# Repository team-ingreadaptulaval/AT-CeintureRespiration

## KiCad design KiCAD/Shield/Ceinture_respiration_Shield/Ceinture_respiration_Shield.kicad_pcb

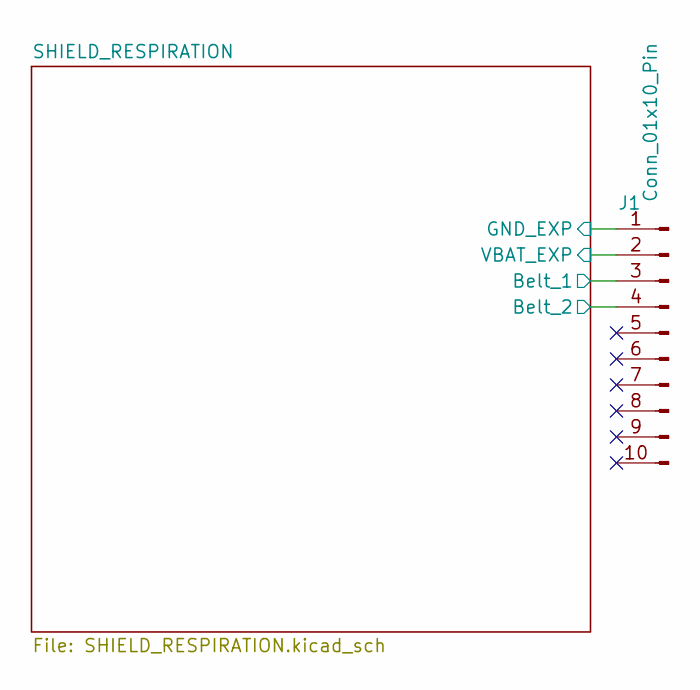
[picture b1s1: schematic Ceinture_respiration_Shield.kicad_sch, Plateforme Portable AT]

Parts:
J1: Conn_01x10_Pin; PinHeader_1x10_P2.54mm_Vertical; LCSC C492409

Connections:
/SHIELD_RESPIRATION/Belt_1: J1.3; also elsewhere on the board
/SHIELD_RESPIRATION/Belt_2: J1.4; also elsewhere on the board
/SHIELD_RESPIRATION/VBAT_EXP: J1.2; also elsewhere on the board
GND_EXP: J1.1; also elsewhere on the board

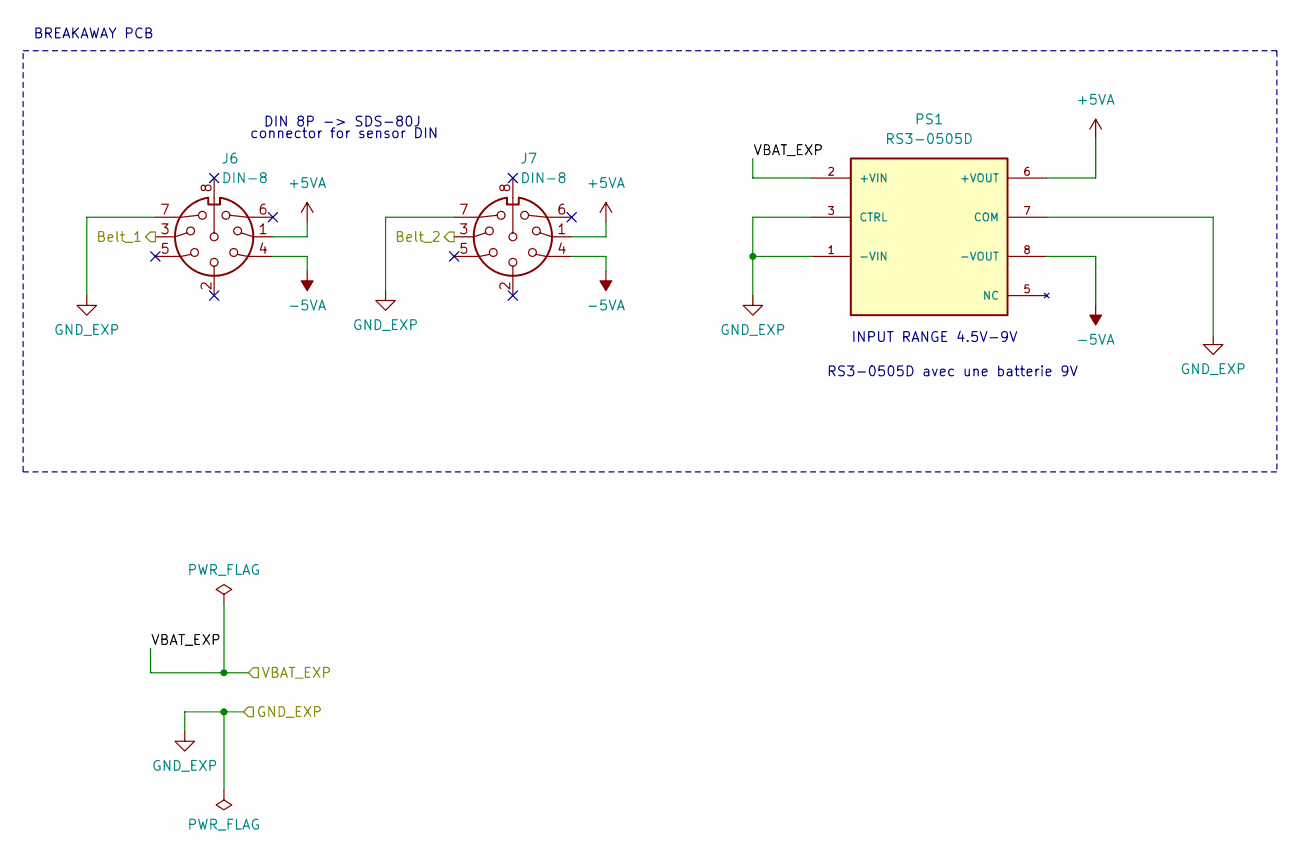
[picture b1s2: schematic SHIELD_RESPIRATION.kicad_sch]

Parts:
J6, J7: DIN-8; CUI_SDS-80J; MPN SDS-80J; Digikey CP-2380-ND
PS1: RS3-0505D; CONV_RS3-0505D; PARTREV 3; Digikey 945-1318-ND

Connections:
+5VA: J6.1, J7.1, PS1.6 (+VOUT)
-5VA: J6.4, J7.4, PS1.8 (-VOUT)
/SHIELD_RESPIRATION/Belt_1: J6.3; also elsewhere on the board
/SHIELD_RESPIRATION/Belt_2: J7.3; also elsewhere on the board
/SHIELD_RESPIRATION/VBAT_EXP: PS1.2 (+VIN); also elsewhere on the board
GND_EXP: J6.7, J7.7, PS1.1 (-VIN), PS1.3 (CTRL), PS1.7 (COM); also elsewhere on the board

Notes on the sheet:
connector for sensor DIN
DIN 8P -> SDS-80J
INPUT RANGE 4.5V-9V
RS3-0505D avec une batterie 9V
BREAKAWAY PCB

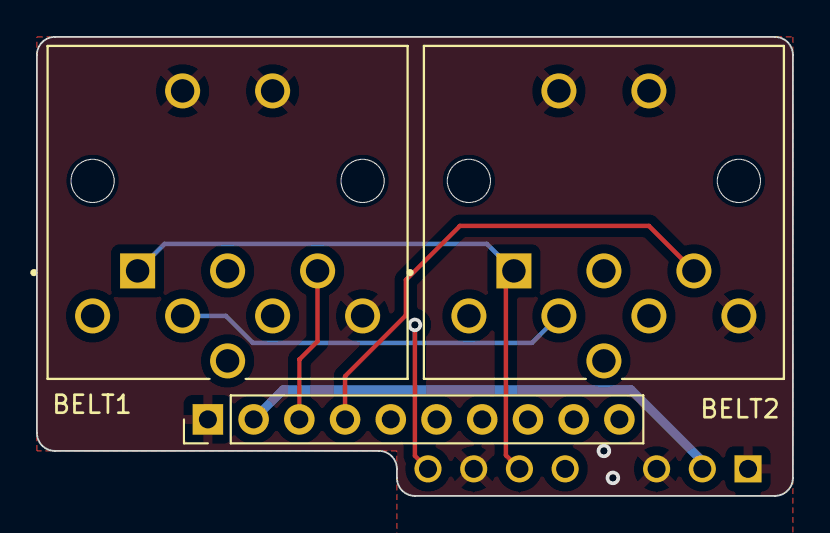
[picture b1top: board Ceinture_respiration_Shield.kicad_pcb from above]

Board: 4 copper layers, 42.0 x 25.5 mm, 4 parts (1 on the bottom side), 6 nets.

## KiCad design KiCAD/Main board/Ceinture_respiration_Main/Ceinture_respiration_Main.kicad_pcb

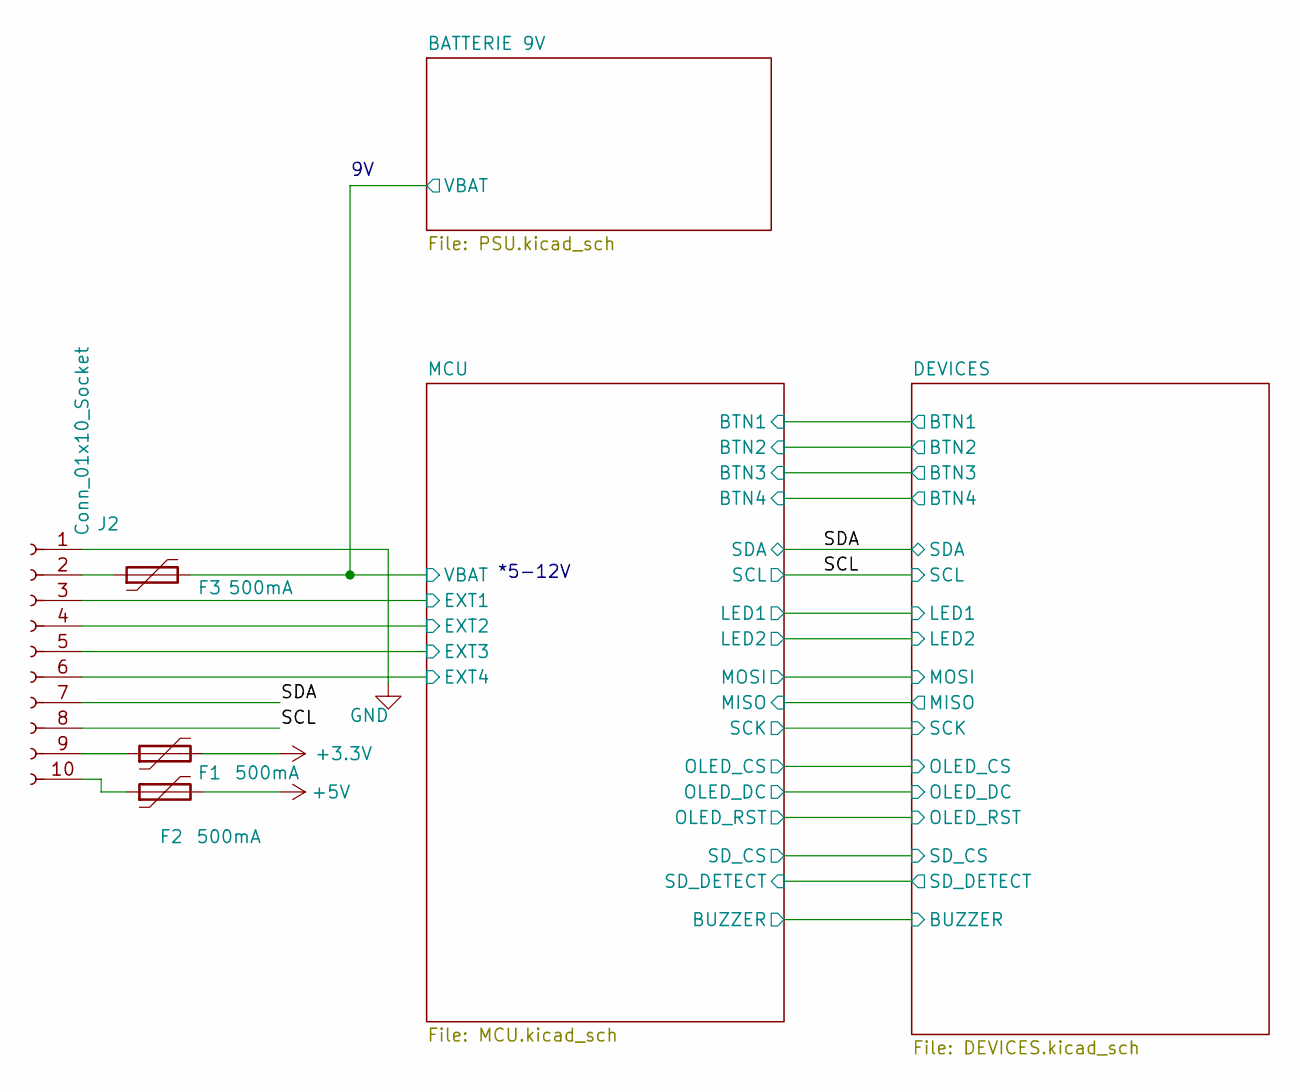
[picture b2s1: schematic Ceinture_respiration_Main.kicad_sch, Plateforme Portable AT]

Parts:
F1, F2, F3: 500mA; Fuse_0603_1608Metric; LCSC C2844464
J2: Conn_01x10_Socket; PinSocket_1x10_P2.54mm_Vertical; LCSC C2897373

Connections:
+3.3V: F1.2; also elsewhere on the board
+5V: F2.2; also elsewhere on the board
/BATTERIE 9V/VBAT: F3.2; also elsewhere on the board
/MCU/EXT1: J2.3; also elsewhere on the board
/MCU/EXT2: J2.4; also elsewhere on the board
/MCU/EXT3: J2.5; also elsewhere on the board
/MCU/EXT4: J2.6; also elsewhere on the board
/SCL: J2.8; also elsewhere on the board
/SDA: J2.7; also elsewhere on the board
GND: J2.1; also elsewhere on the board
unnamed: F3.1, J2.2
unnamed: F1.1, J2.9
unnamed: F2.1, J2.10

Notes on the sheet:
*5-12V

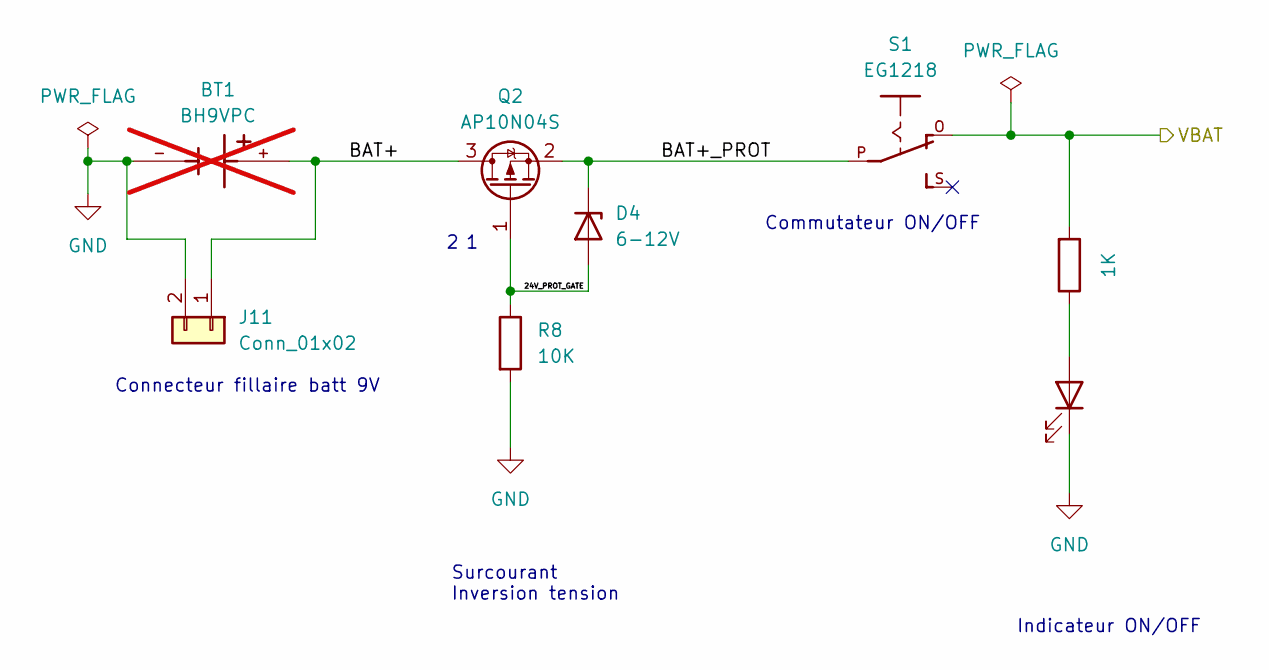
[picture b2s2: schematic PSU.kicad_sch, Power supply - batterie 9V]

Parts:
BT1: BH9VPC; BAT_BH9VPC; PARTREV F; not fitted
D4: 6-12V; D_SOD-323; LCSC C2103
D5: LED; LED_D3.0mm; LCSC C2895472
J11: Conn_01x02; PinHeader_1x02_P2.54mm_Vertical
Q2: AP10N04S; SOT-23; LCSC C15127
R8: 10K; R_0603_1608Metric; LCSC C25804
R9: 1K; R_0603_1608Metric; LCSC C21190
S1: EG1218; MPN EG1218; DigiKey EG1218

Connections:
/BATTERIE 9V/24V_PROT_GATE: D4.2 (A), Q2.1 (G), R8.1
/BATTERIE 9V/BAT+: J11.1, Q2.3 (D)
/BATTERIE 9V/BAT+_PROT: D4.1 (K), Q2.2 (S), S1.P
/BATTERIE 9V/VBAT: R9.2, S1.O; also elsewhere on the board
GND: D5.1 (K), J11.2, R8.2; also elsewhere on the board
unnamed: D5.2 (A), R9.1

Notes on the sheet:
Connecteur fillaire batt 9V
Commutateur ON/OFF
Indicateur ON/OFF
Surcourant Inversion tension

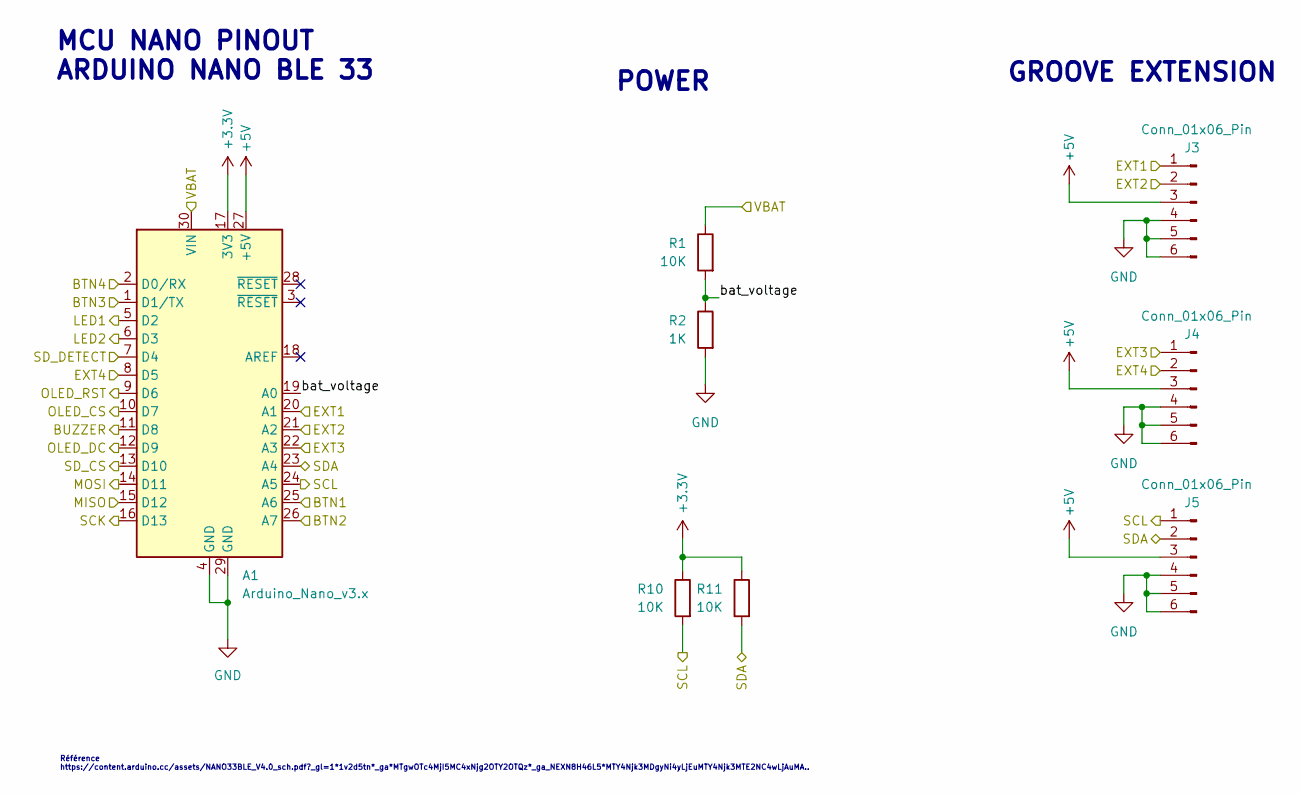
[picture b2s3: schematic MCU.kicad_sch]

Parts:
A1: Arduino_Nano_v3.x; MODULE_ABX00027
J3, J4, J5: Conn_01x06_Pin; CONN4_20164_SEE; MPN Grove Conn
R1, R10, R11: 10K; R_0603_1608Metric; LCSC C25804
R2: 1K; R_0603_1608Metric; LCSC C21190

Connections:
+3.3V: A1.17 (3V3), R10.1, R11.1; also elsewhere on the board
+5V: A1.27 (+5V), J3.3, J4.3, J5.3; also elsewhere on the board
/BATTERIE 9V/VBAT: A1.30 (VIN), R1.1; also elsewhere on the board
/DEVICES/BTN1: A1.25 (A6); also elsewhere on the board
/DEVICES/BTN2: A1.26 (A7); also elsewhere on the board
/DEVICES/BTN3: A1.1 (D1/TX); also elsewhere on the board
/DEVICES/BTN4: A1.2 (D0/RX); also elsewhere on the board
/DEVICES/BUZZER: A1.11 (D8); also elsewhere on the board
/DEVICES/LED1: A1.5 (D2); also elsewhere on the board
/DEVICES/LED2: A1.6 (D3); also elsewhere on the board
/DEVICES/MISO: A1.15 (D12); also elsewhere on the board
/DEVICES/MOSI: A1.14 (D11); also elsewhere on the board
/DEVICES/OLED_CS: A1.10 (D7); also elsewhere on the board
/DEVICES/OLED_DC: A1.12 (D9); also elsewhere on the board
/DEVICES/OLED_RST: A1.9 (D6); also elsewhere on the board
/DEVICES/SCK: A1.16 (D13); also elsewhere on the board
/DEVICES/SD_CS: A1.13 (D10); also elsewhere on the board
/DEVICES/SD_DETECT: A1.7 (D4); also elsewhere on the board
/MCU/EXT1: A1.20 (A1), J3.1; also elsewhere on the board
/MCU/EXT2: A1.21 (A2), J3.2; also elsewhere on the board
/MCU/EXT3: A1.22 (A3), J4.1; also elsewhere on the board
/MCU/EXT4: A1.8 (D5), J4.2; also elsewhere on the board
/MCU/bat_voltage: A1.19 (A0), R1.2, R2.1
/SCL: A1.24 (A5), J5.1, R10.2; also elsewhere on the board
/SDA: A1.23 (A4), J5.2, R11.2; also elsewhere on the board
GND: A1.4 (GND), A1.29 (GND), J3.4, J3.5, J3.6, J4.4, J4.5, J4.6, J5.4, J5.5, J5.6, R2.2; also elsewhere on the board

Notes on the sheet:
MCU NANO PINOUT ARDUINO NANO BLE 33
Référence https://content.arduino.cc/assets/NANO33BLE_V4.0_sch.pdf?_gl=1*1v2d5tn*_ga*MTgwOTc4MjI5MC4xNjg2OTY2OTQz*_ga_NEXN8H46L5*MTY4Njk3MDgyNi4yLjEuMTY4Njk3MTE2NC4wLjAuMA..
GROOVE EXTENSION
POWER

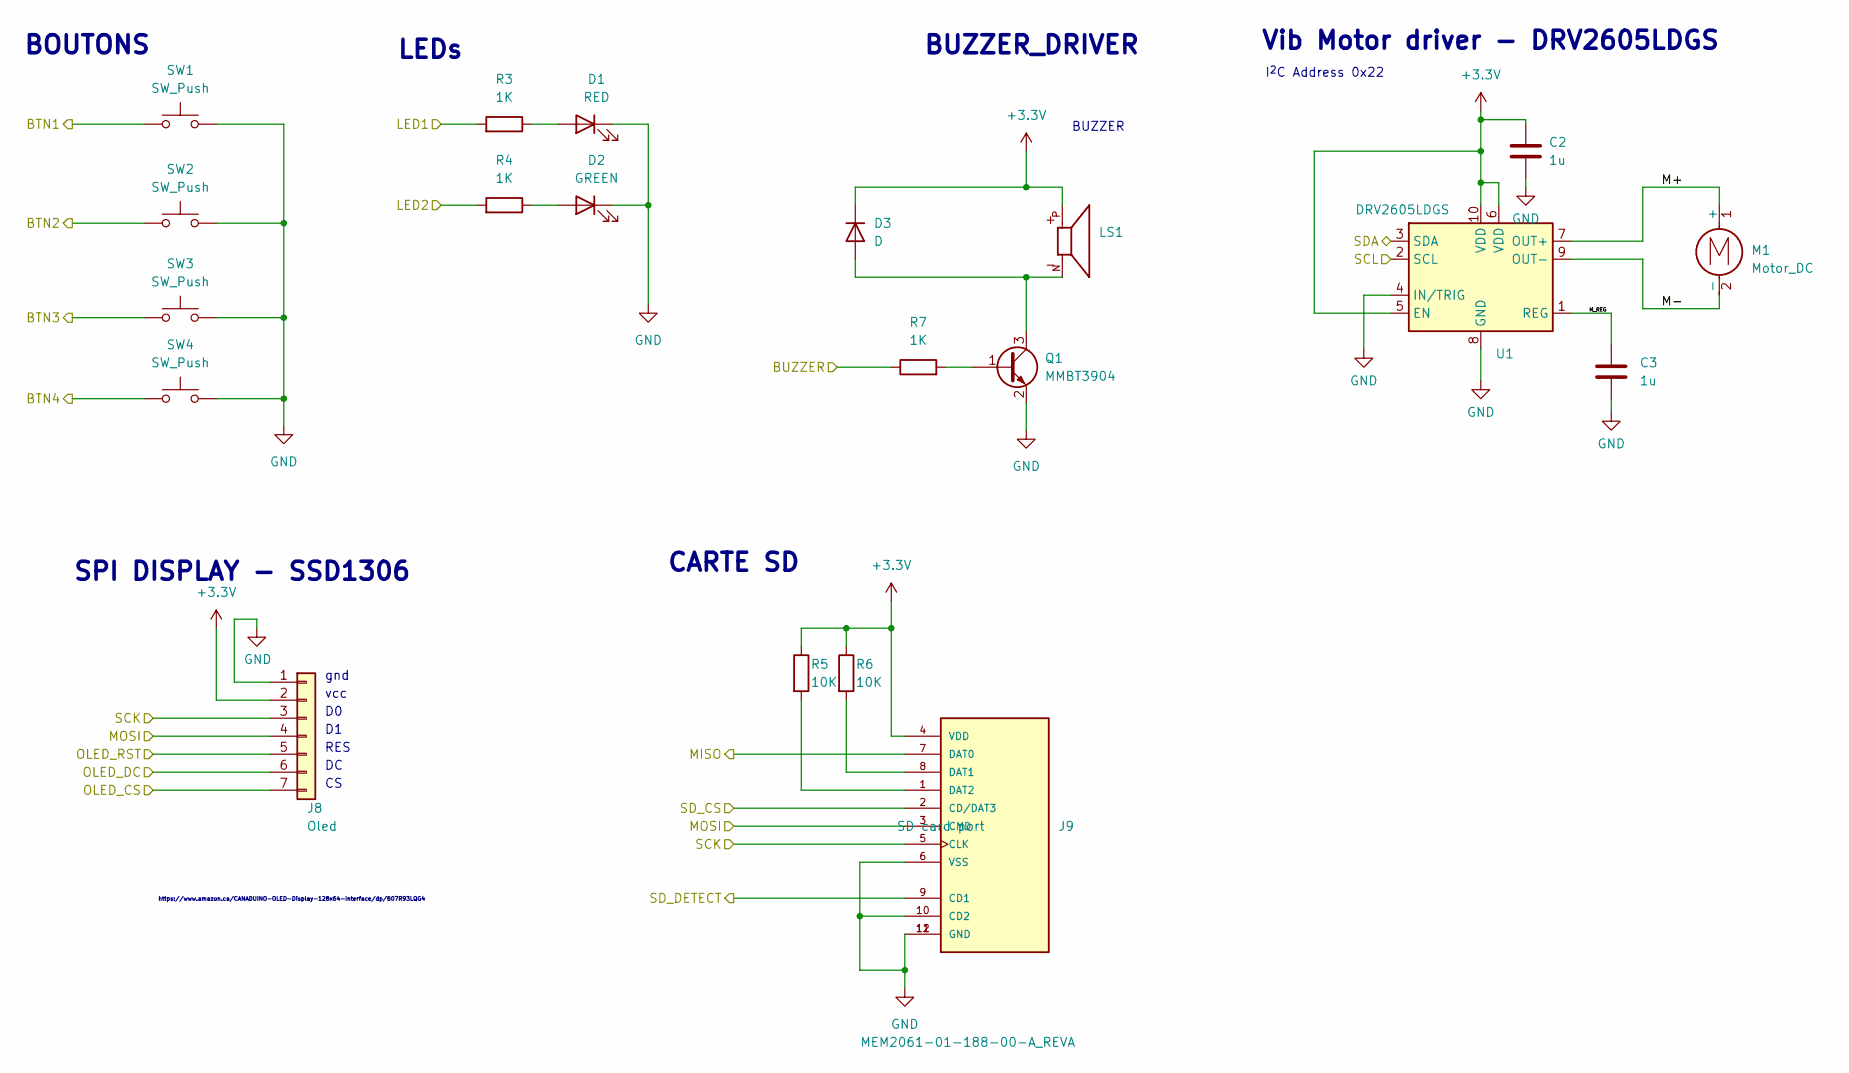
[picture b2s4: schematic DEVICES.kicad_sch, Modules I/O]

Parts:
C2, C3: 1u; C_0603_1608Metric; LCSC C15849
D1: RED; LED_D3.0mm; LCSC C779429
D2: GREEN; LED_D3.0mm; LCSC C2895476
D3: D; D_SOD-323F; LCSC C191023
J8: Oled; Adafruit_SSD1306_SPI; MPN AOM12864A0-0.96WW-ANO / ER-OLEDM0.96-1B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; Digikey AOM12864A0-0.96WW-ANO
J9: MEM2061-01-188-00-A_REVA; GCT_MEM2061-01-188-00-A_REVA; MPN MEM2061-01-188-00-A_REVA; LCSC C5151738
LS1: XDCR_CMT-7525-80-SMT-TR; LCSC C189208
M1: Motor_DC; XDCR_C0720B001F; MPN VC0720B001F
Q1: MMBT3904; SOT-23; LCSC C20526
R3, R4, R7: 1K; R_0603_1608Metric; LCSC C21190
R5, R6: 10K; R_0603_1608Metric; LCSC C25804
SW1, SW2, SW3, SW4: SW_Push; SW_SPST_TL3305B; LCSC C2939211
U1: DRV2605LDGS; VSSOP-10_3x3mm_P0.5mm; LCSC C527464

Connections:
+3.3V: C2.1, D3.1 (K), J8.2, J9.4 (VDD), LS1.P, R5.1, R6.1, U1.5 (EN), U1.6 (VDD), U1.10 (VDD); also elsewhere on the board
/DEVICES/BTN1: SW1.1; also elsewhere on the board
/DEVICES/BTN2: SW2.1; also elsewhere on the board
/DEVICES/BTN3: SW3.1; also elsewhere on the board
/DEVICES/BTN4: SW4.1; also elsewhere on the board
/DEVICES/BUZZER: R7.1; also elsewhere on the board
/DEVICES/LED1: R3.2; also elsewhere on the board
/DEVICES/LED2: R4.2; also elsewhere on the board
/DEVICES/M+: M1.1 (+), U1.7 (OUT+)
/DEVICES/M-: M1.2 (-), U1.9 (OUT-)
/DEVICES/MISO: J9.7 (DAT0); also elsewhere on the board
/DEVICES/MOSI: J8.4, J9.3 (CMD); also elsewhere on the board
/DEVICES/M_REG: C3.1, U1.1 (REG)
/DEVICES/OLED_CS: J8.7; also elsewhere on the board
/DEVICES/OLED_DC: J8.6; also elsewhere on the board
/DEVICES/OLED_RST: J8.5; also elsewhere on the board
/DEVICES/SCK: J8.3, J9.5 (CLK); also elsewhere on the board
/DEVICES/SD_CS: J9.2 (CD/DAT3); also elsewhere on the board
/DEVICES/SD_DETECT: J9.9 (CD1); also elsewhere on the board
/SCL: U1.2 (SCL); also elsewhere on the board
/SDA: U1.3 (SDA); also elsewhere on the board
GND: C2.2, C3.2, D1.1 (K), D2.1 (K), J8.1, J9.6 (VSS), J9.10 (CD2), J9.11 (GND), J9.12 (GND), Q1.2 (E), SW1.2, SW2.2, SW3.2, SW4.2, U1.4 (IN/TRIG), U1.8 (GND); also elsewhere on the board
unnamed: D1.2 (A), R3.1
unnamed: D2.2 (A), R4.1
unnamed: D3.2 (A), LS1.N, Q1.3 (C)
unnamed: J9.8 (DAT1), R6.2
unnamed: J9.1 (DAT2), R5.2
unnamed: Q1.1 (B), R7.2

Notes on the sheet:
BUZZER_DRIVER
I^{2}C Address 0x22
gnd
LEDs
vcc
Vib Motor driver - DRV2605LDGS
SPI DISPLAY - SSD1306
BOUTONS
RES
BUZZER
https://www.amazon.ca/CANADUINO-OLED-Display-128x64-Interface/dp/B07R93LQG4
CARTE SD

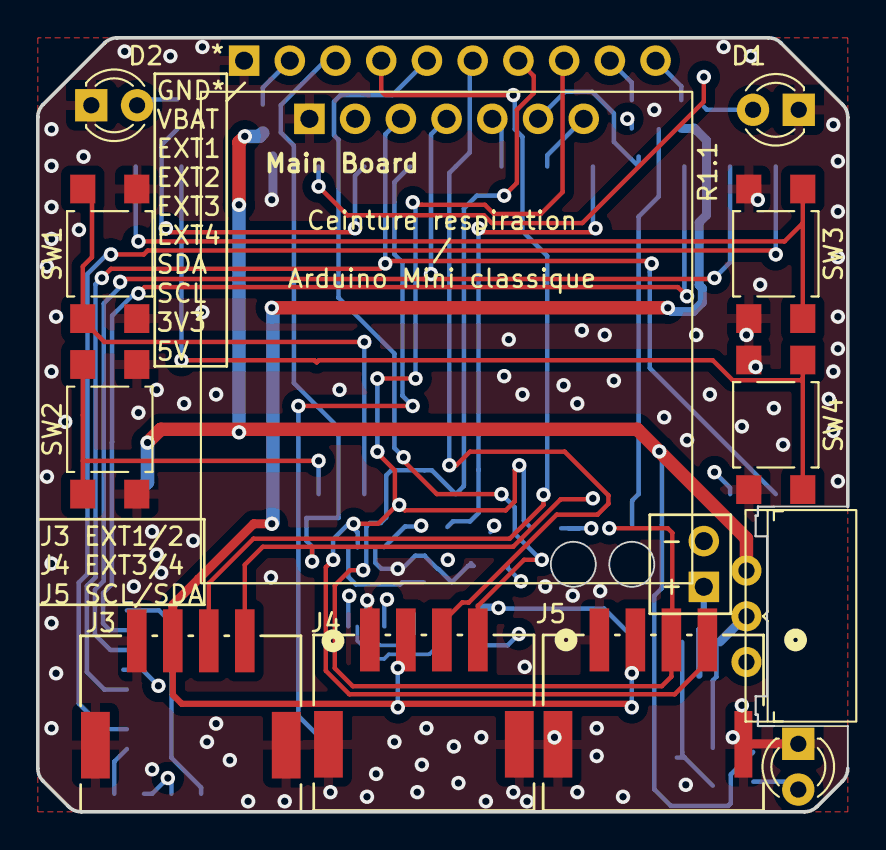
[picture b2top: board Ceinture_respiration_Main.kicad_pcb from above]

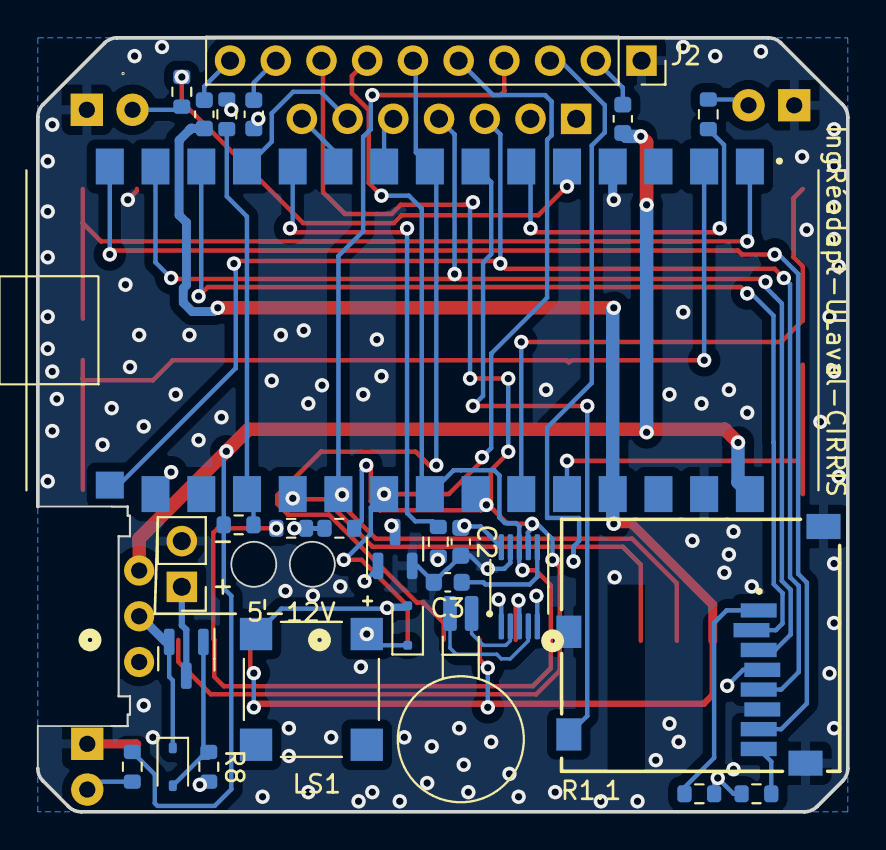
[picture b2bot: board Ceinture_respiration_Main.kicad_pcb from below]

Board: 4 copper layers, 45.0 x 43.0 mm, 39 parts (27 on the bottom side), 42 nets.

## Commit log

2023-05-19 Basic Architecture and search of parts
2023-06-22 First draft PCB and sch
2023-06-22 Cleanup files
2023-07-21 Scématique complété
    Reste quelques footprint à configurer
2023-07-21 Schématique prête pour design review
2023-09-01 Schematique 99%, PCB 50%
    schématique complété, nettoyé et layout complété, reste routage
2023-09-01 sch 99% pcb 85%
    Ajout de l'ensemble des traces du pcb mère
    Ajout de via stiching
    Reste le PCB shield à terminer
    Reste les erreurs générés à nettoyer
    Brûlé le gars...
2023-09-01 sch 99% pcb 99%
    Reste à préparer les commandes
2023-09-01 PCB sent for production
    See latest production files.
2023-09-23 Conception du boitier et documentation
    Boitier impression #2
2023-10-15 Ajout version de case sans shield
2025-06-04 Ajout firmware Arduino
2025-06-09 SSéparé design en 2 pcb distinct
2025-06-10 modifié info Part number du main board pour faciliter la génération de BOM non JLC
2025-06-10 Changé # pièce switch sur main board poru utiliser pièces en stock.
2025-06-10 ajouté fichiers oublier
2025-06-10 ajouté # de pièces option 2 de connectgeur batterie 9V
